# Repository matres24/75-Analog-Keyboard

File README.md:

# 75%-Analog-Keyboard
A custom-built mechanical keyboard featuring Hall effect sensors for analog key press detection. This project uses DRV5055A4 Hall sensors, magnets mounted in keycaps, and a CD74HC4067 multiplexer controlled by a microcontroller. Each key press is measured as a variable voltage, enabling analog input functionality. RGB LEDs (WS2812B) provide per-key lighting. This project is meant to fit into Monsgeek M1 case.

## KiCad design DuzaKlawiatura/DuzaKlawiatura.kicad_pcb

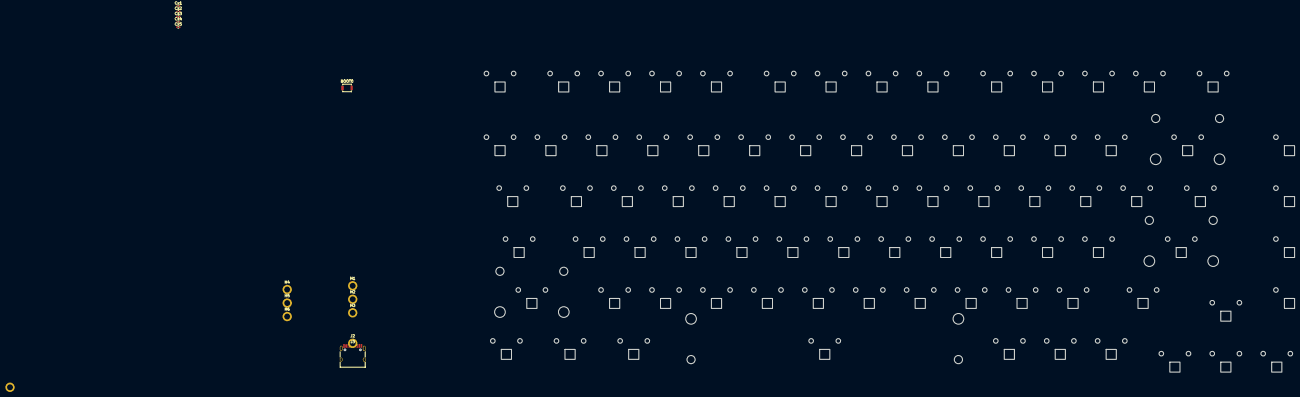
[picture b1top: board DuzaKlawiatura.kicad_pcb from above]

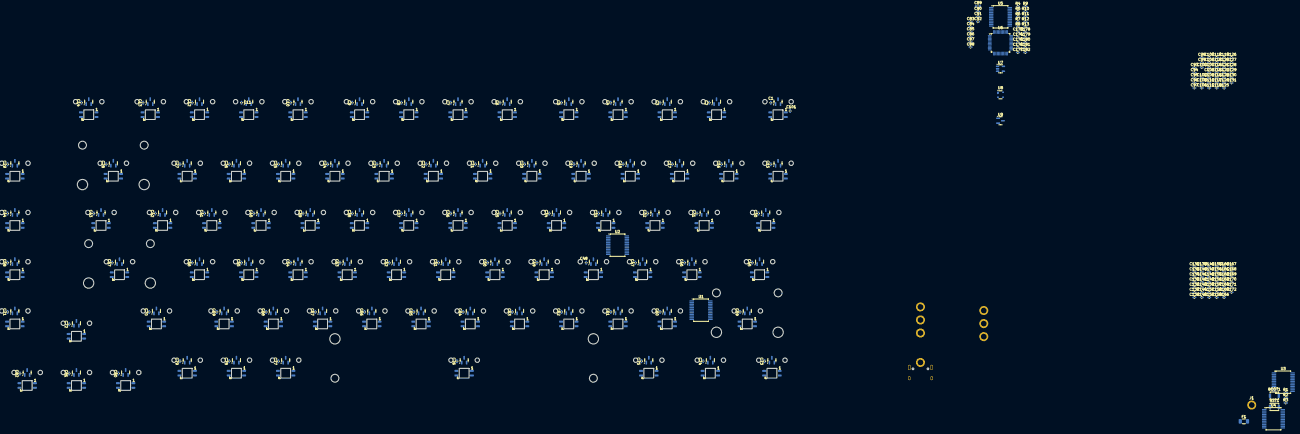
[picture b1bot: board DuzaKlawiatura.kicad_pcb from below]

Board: 2 copper layers, 386 parts (208 on the bottom side), 31 nets, no tracks yet.

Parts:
BOOT0, BOOT1: SW_SPST; SW_SPST_B3U-1000P
C1, C2, C3, C4, C5, C6, C7, C8, C9, C10, C11, C12, C13, C14, C15, C16, C17, C18, C19, C20, C21, C22, C23, C24, C25, C26, C27, C28, C29, C30, C31, C32, C33, C34, C35, C36, C37, C38, C39, C40, C41, C42, C43, C44, C45, C46, C47, C48, C49, C50, C51, C52, C53, C54, C55, C56, C57, C58, C59, C60, C61, C62, C63, C64, C65, C66, C67, C68, C69, C70, C71, C72, C73, C74, C75, C76, C77, C78, C79, C80, C81, C82, C98, C99, C100: 0,1u; C_0402_1005Metric
C83, C85, C86, C87: 10n; C_0402_1005Metric
C84: 10uF; C_0402_1005Metric
C88, C90, C91, C92, C93, C94, C97: 100nF; C_0402_1005Metric
C89: 10uF; C_0603_1608Metric
C95, C96: 1uF; C_0402_1005Metric
C101, C102, C103, C104, C105, C106, C107, C108, C109, C110, C111, C112, C113, C114, C115, C116, C117, C118, C119, C120, C121, C122, C123, C124, C125, C126, C127, C128, C129, C130, C131, C132, C133, C134, C135, C136, C137, C138, C139, C140, C141, C142, C143, C144, C145, C146, C147, C148, C149, C150, C151, C152, C153, C154, C155, C156, C157, C158, C159, C160, C161, C162, C163, C164, C165, C166, C167, C168, C169, C170, C171, C172, C173, C174, C175, C176, C177, C178, C179, C180, C181, C182: 100n; C_0402_1005Metric
Cx1, Cx2, Cx3, Cx4, Cx5: 100nF; C_0402_1005Metric
F1: 500mA; Fuse_1206_3216Metric
H1, H2, H3, H4, H5, H6: MountingHole; MountingHole_2.2mm_M2_ISO7380_Pad
J1, J2: Conn_01x02_Pin; MountingHole_2.2mm_M2_ISO7380_Pad
J3: USB_C_Receptacle_USB2.0; USB_C_Receptacle_HRO_TYPE-C-31-M-12
LED1, LED2, LED3, LED4, LED5, LED6, LED7, LED8, LED9, LED10, LED11, LED12, LED13, LED14, LED15, LED16, LED17, LED18, LED19, LED20, LED21, LED22, LED23, LED24, LED25, LED26, LED27, LED28, LED29, LED30, LED31, LED32, LED33, LED34, LED35, LED36, LED37, LED38, LED39, LED40, LED41, LED42, LED43, LED44, LED45, LED46, LED47, LED48, LED49, LED50, LED51, LED52, LED53, LED54, LED55, LED56, LED57, LED58, LED59, LED60, LED61, LED62, LED63, LED64, LED65, LED66, LED67, LED68, LED69, LED70, LED71, LED72, LED73, LED74, LED75, LED76, LED77, LED78, LED79, LED80, LED81, LED82: WS2812B; MX-LED_WS2812B_wide
R1, R2, R3, R4, R5, R6, R7, R8, R9, R10, R13: 10k; R_0402_1005Metric
R11, R12: 5.1k; R_0402_1005Metric
RST1: SW_SPST; SW_SPST_B3U-1000P
SW1, SW2, SW3, SW4, SW5, SW6, SW7, SW8, SW9, SW10, SW11, SW12, SW13, SW14, SW15, SW16, SW17, SW18, SW19, SW20, SW21, SW22, SW23, SW24, SW25, SW26, SW27, SW29, SW31, SW32, SW33, SW34, SW35, SW36, SW37, SW38, SW39, SW40, SW41, SW42, SW44, SW46, SW47, SW48, SW49, SW50, SW51, SW52, SW53, SW54, SW55, SW56, SW58, SW60, SW61, SW62, SW63, SW64, SW65, SW66, SW67, SW68, SW69, SW71, SW72, SW77, SW78, SW79, SW80, SW81, SW82: DRV5053; MX-Analog-1U
SW28: DRV5053; MX-Analog-2U
SW30, SW43: DRV5053; MX-Analog-1.5U
SW45, SW70: DRV5053; MX-Analog-1.75U
SW57, SW59: DRV5053; MX-Analog-2.25U
SW73, SW74, SW75: DRV5053; MX-Analog-1.25U
SW76: DRV5053; MX-Analog-6.25U-ReversedStabilizers
U1, U2, U3, U4, U5: CD74HC4067SM; SSOP-24_5.3x8.2mm_P0.65mm
U6: STM32F072CBT6; LQFP-48_7x7mm_P0.5mm
U7: SN74LV1T34DBV; SOT-23-5
U8: PRTR5V0U2X; SOT-143
U9: XC6206P332MR-Regulator_Linear; SOT-23

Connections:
+3V3: BOOT0.1 (A), BOOT1.1 (A), C89.1, C90.1, C91.1, C92.1, C93.1, C96.1, C97.1, U6.1 (VBAT), U6.9 (VDDA), U6.24 (VDD), U6.36 (VDDIO2), U6.48 (VDD), U9.2 (VO)
+5V: C1.1, C2.1, C3.1, C4.1, C5.1, C6.1, C7.1, C8.1, C9.1, C10.1, C11.1, C12.1, C13.1, C14.1, C15.1, C16.1, C17.1, C18.1, C19.1, C20.1, C21.1, C22.1, C23.1, C24.1, C25.1, C26.1, C27.1, C28.1, C29.1, C30.1, C31.1, C32.1, C33.1, C34.1, C35.1, C36.1, C37.1, C38.1, C39.1, C40.1, C41.1, C42.1, C43.1, C44.1, C45.1, C46.1, C47.1, C48.1, C49.1, C50.1, C51.1, C52.1, C53.1, C54.1, C55.1, C56.1, C57.1, C58.1, C59.1, C60.1, C61.1, C62.1, C63.1, C64.1, C65.1, C66.1, C67.1, C68.1, C69.1, C70.1, C71.1, C72.1, C73.1, C74.1, C75.1, C76.1, C77.1, C78.1, C79.1, C80.1, C81.1, C82.1, C88.1, C95.1, C98.1, C99.1, C100.1, C101.1, C102.1, C103.1, C104.1, C105.1, C106.1, C107.1, C108.1, C109.1, C110.1, C111.1, C112.1, C113.1, C114.1, C115.1, C116.1, C117.1, C118.1, C119.1, C120.1, C121.1, C122.1, C123.1, C124.1, C125.1, C126.1, C127.1, C128.1, C129.1, C130.1, C131.1, C132.1, C133.1, C134.1, C135.1, C136.1, C137.1, C138.1, C139.1, C140.1, C141.1, C142.1, C143.1, C144.1, C145.1, C146.1, C147.1, C148.1, C149.1, C150.1, C151.1, C152.1, C153.1, C154.1, C155.1, C156.1, C157.1, C158.1, C159.1, C160.1, C161.1, C162.1, C163.1, C164.1, C165.1, C166.1, C167.1, C168.1, C169.1, C170.1, C171.1, C172.1, C173.1, C174.1, C175.1, C176.1, C177.1, C178.1, C179.1, C180.1, C181.1, C182.1, Cx1.2, Cx2.2, Cx3.2, Cx4.2, Cx5.2, F1.2, LED1.1 (VCC), LED2.1 (VCC), LED3.1 (VCC), LED4.1 (VCC), LED5.1 (VCC), LED6.1 (VCC), LED7.1 (VCC), LED8.1 (VCC), LED9.1 (VCC), LED10.1 (VCC), LED11.1 (VCC), LED12.1 (VCC), LED13.1 (VCC), LED14.1 (VCC), LED15.1 (VCC), LED16.1 (VCC), LED17.1 (VCC), LED18.1 (VCC), LED19.1 (VCC), LED20.1 (VCC), LED21.1 (VCC), LED22.1 (VCC), LED23.1 (VCC), LED24.1 (VCC), LED25.1 (VCC), LED26.1 (VCC), LED27.1 (VCC), LED28.1 (VCC), LED29.1 (VCC), LED30.1 (VCC), LED31.1 (VCC), LED32.1 (VCC), LED33.1 (VCC), LED34.1 (VCC), LED35.1 (VCC), LED36.1 (VCC), LED37.1 (VCC), LED38.1 (VCC), LED39.1 (VCC), LED40.1 (VCC), LED41.1 (VCC), LED42.1 (VCC), LED43.1 (VCC), LED44.1 (VCC), LED45.1 (VCC), LED46.1 (VCC), LED47.1 (VCC), LED48.1 (VCC), LED49.1 (VCC), LED50.1 (VCC), LED51.1 (VCC), LED52.1 (VCC), LED53.1 (VCC), LED54.1 (VCC), LED55.1 (VCC), LED56.1 (VCC), LED57.1 (VCC), LED58.1 (VCC), LED59.1 (VCC), LED60.1 (VCC), LED61.1 (VCC), LED62.1 (VCC), LED63.1 (VCC), LED64.1 (VCC), LED65.1 (VCC), LED66.1 (VCC), LED67.1 (VCC), LED68.1 (VCC), LED69.1 (VCC), LED70.1 (VCC), LED71.1 (VCC), LED72.1 (VCC), LED73.1 (VCC), LED74.1 (VCC), LED75.1 (VCC), LED76.1 (VCC), LED77.1 (VCC), LED78.1 (VCC), LED79.1 (VCC), LED80.1 (VCC), LED81.1 (VCC), LED82.1 (VCC), SW1.1 (VCC), SW2.1 (VCC), SW3.1 (VCC), SW4.1 (VCC), SW5.1 (VCC), SW6.1 (VCC), SW7.1 (VCC), SW8.1 (VCC), SW9.1 (VCC), SW10.1 (VCC), SW11.1 (VCC), SW12.1 (VCC), SW13.1 (VCC), SW14.1 (VCC), SW15.1 (VCC), SW16.1 (VCC), SW17.1 (VCC), SW18.1 (VCC), SW19.1 (VCC), SW20.1 (VCC), SW21.1 (VCC), SW22.1 (VCC), SW23.1 (VCC), SW24.1 (VCC), SW25.1 (VCC), SW26.1 (VCC), SW27.1 (VCC), SW28.1 (VCC), SW29.1 (VCC), SW30.1 (VCC), SW31.1 (VCC), SW32.1 (VCC), SW33.1 (VCC), SW34.1 (VCC), SW35.1 (VCC), SW36.1 (VCC), SW37.1 (VCC), SW38.1 (VCC), SW39.1 (VCC), SW40.1 (VCC), SW41.1 (VCC), SW42.1 (VCC), SW43.1 (VCC), SW44.1 (VCC), SW45.1 (VCC), SW46.1 (VCC), SW47.1 (VCC), SW48.1 (VCC), SW49.1 (VCC), SW50.1 (VCC), SW51.1 (VCC), SW52.1 (VCC), SW53.1 (VCC), SW54.1 (VCC), SW55.1 (VCC), SW56.1 (VCC), SW57.1 (VCC), SW58.1 (VCC), SW59.1 (VCC), SW60.1 (VCC), SW61.1 (VCC), SW62.1 (VCC), SW63.1 (VCC), SW64.1 (VCC), SW65.1 (VCC), SW66.1 (VCC), SW67.1 (VCC), SW68.1 (VCC), SW69.1 (VCC), SW70.1 (VCC), SW71.1 (VCC), SW72.1 (VCC), SW73.1 (VCC), SW74.1 (VCC), SW75.1 (VCC), SW76.1 (VCC), SW77.1 (VCC), SW78.1 (VCC), SW79.1 (VCC), SW80.1 (VCC), SW81.1 (VCC), SW82.1 (VCC), U1.24 (VCC), U2.24 (VCC), U3.24 (VCC), U4.24 (VCC), U5.24 (VCC), U7.5 (VCC), U8.4 (VCC), U9.3 (VI)
BOOT0: BOOT0.2 (B), BOOT1.2 (B), R13.1, U6.44 (BOOT0)
COM: C83.1, R1.2, R4.1, U6.11 (PA1)
COM1: C84.1, R2.2, R5.1, U6.12 (PA2)
COM2: C85.1, R3.2, R6.1, U6.13 (PA3)
COM3: C86.1, R7.2, R9.1, U6.14 (PA4)
COM4: C87.1, R8.2, R10.1, U6.15 (PA5)
D+: J3.A6 (D+), J3.B6 (D+), U6.33 (PA12), U8.3 (I/O2)
D-: J3.A7 (D-), J3.B7 (D-), U6.32 (PA11), U8.2 (I/O1)
E: U1.15 (~E), U6.40 (PB4)
E1: U2.15 (~E), U6.41 (PB5)
E2: U3.15 (~E), U6.42 (PB6)
E3: U4.15 (~E), U6.43 (PB7)
E4: U5.15 (~E), U6.45 (PB8)
GND: C1.2, C2.2, C3.2, C4.2, C5.2, C6.2, C7.2, C8.2, C9.2, C10.2, C11.2, C12.2, C13.2, C14.2, C15.2, C16.2, C17.2, C18.2, C19.2, C20.2, C21.2, C22.2, C23.2, C24.2, C25.2, C26.2, C27.2, C28.2, C29.2, C30.2, C31.2, C32.2, C33.2, C34.2, C35.2, C36.2, C37.2, C38.2, C39.2, C40.2, C41.2, C42.2, C43.2, C44.2, C45.2, C46.2, C47.2, C48.2, C49.2, C50.2, C51.2, C52.2, C53.2, C54.2, C55.2, C56.2, C57.2, C58.2, C59.2, C60.2, C61.2, C62.2, C63.2, C64.2, C65.2, C66.2, C67.2, C68.2, C69.2, C70.2, C71.2, C72.2, C73.2, C74.2, C75.2, C76.2, C77.2, C78.2, C79.2, C80.2, C81.2, C82.2, C83.2, C84.2, C85.2, C86.2, C87.2, C88.2, C89.2, C90.2, C91.2, C92.2, C93.2, C94.2, C95.2, C96.2, C97.2, C98.2, C99.2, C100.2, C101.2, C102.2, C103.2, C104.2, C105.2, C106.2, C107.2, C108.2, C109.2, C110.2, C111.2, C112.2, C113.2, C114.2, C115.2, C116.2, C117.2, C118.2, C119.2, C120.2, C121.2, C122.2, C123.2, C124.2, C125.2, C126.2, C127.2, C128.2, C129.2, C130.2, C131.2, C132.2, C133.2, C134.2, C135.2, C136.2, C137.2, C138.2, C139.2, C140.2, C141.2, C142.2, C143.2, C144.2, C145.2, C146.2, C147.2, C148.2, C149.2, C150.2, C151.2, C152.2, C153.2, C154.2, C155.2, C156.2, C157.2, C158.2, C159.2, C160.2, C161.2, C162.2, C163.2, C164.2, C165.2, C166.2, C167.2, C168.2, C169.2, C170.2, C171.2, C172.2, C173.2, C174.2, C175.2, C176.2, C177.2, C178.2, C179.2, C180.2, C181.2, C182.2, Cx1.1, Cx2.1, Cx3.1, Cx4.1, Cx5.1, J3.A1 (GND), J3.A12 (GND), J3.B1 (GND), J3.B12 (GND), J3.S1 (SHIELD), LED1.3 (GND), LED2.3 (GND), LED3.3 (GND), LED4.3 (GND), LED5.3 (GND), LED6.3 (GND), LED7.3 (GND), LED8.3 (GND), LED9.3 (GND), LED10.3 (GND), LED11.3 (GND), LED12.3 (GND), LED13.3 (GND), LED14.3 (GND), LED15.3 (GND), LED16.3 (GND), LED17.3 (GND), LED18.3 (GND), LED19.3 (GND), LED20.3 (GND), LED21.3 (GND), LED22.3 (GND), LED23.3 (GND), LED24.3 (GND), LED25.3 (GND), LED26.3 (GND), LED27.3 (GND), LED28.3 (GND), LED29.3 (GND), LED30.3 (GND), LED31.3 (GND), LED32.3 (GND), LED33.3 (GND), LED34.3 (GND), LED35.3 (GND), LED36.3 (GND), LED37.3 (GND), LED38.3 (GND), LED39.3 (GND), LED40.3 (GND), LED41.3 (GND), LED42.3 (GND), LED43.3 (GND), LED44.3 (GND), LED45.3 (GND), LED46.3 (GND), LED47.3 (GND), LED48.3 (GND), LED49.3 (GND), LED50.3 (GND), LED51.3 (GND), LED52.3 (GND), LED53.3 (GND), LED54.3 (GND), LED55.3 (GND), LED56.3 (GND), LED57.3 (GND), LED58.3 (GND), LED59.3 (GND), LED60.3 (GND), LED61.3 (GND), LED62.3 (GND), LED63.3 (GND), LED64.3 (GND), LED65.3 (GND), LED66.3 (GND), LED67.3 (GND), LED68.3 (GND), LED69.3 (GND), LED70.3 (GND), LED71.3 (GND), LED72.3 (GND), LED73.3 (GND), LED74.3 (GND), LED75.3 (GND), LED76.3 (GND), LED77.3 (GND), LED78.3 (GND), LED79.3 (GND), LED80.3 (GND), LED81.3 (GND), LED82.3 (GND), R4.2, R5.2, R6.2, R9.2, R10.2, R11.1, R12.2, R13.2, RST1.2 (B), SW1.3 (GND), SW2.3 (GND), SW3.3 (GND), SW4.3 (GND), SW5.3 (GND), SW6.3 (GND), SW7.3 (GND), SW8.3 (GND), SW9.3 (GND), SW10.3 (GND), SW11.3 (GND), SW12.3 (GND), SW13.3 (GND), SW14.3 (GND), SW15.3 (GND), SW16.3 (GND), SW17.3 (GND), SW18.3 (GND), SW19.3 (GND), SW20.3 (GND), SW21.3 (GND), SW22.3 (GND), SW23.3 (GND), SW24.3 (GND), SW25.3 (GND), SW26.3 (GND), SW27.3 (GND), SW28.3 (GND), SW29.3 (GND), SW30.3 (GND), SW31.3 (GND), SW32.3 (GND), SW33.3 (GND), SW34.3 (GND), SW35.3 (GND), SW36.3 (GND), SW37.3 (GND), SW38.3 (GND), SW39.3 (GND), SW40.3 (GND), SW41.3 (GND), SW42.3 (GND), SW43.3 (GND), SW44.3 (GND), SW45.3 (GND), SW46.3 (GND), SW47.3 (GND), SW48.3 (GND), SW49.3 (GND), SW50.3 (GND), SW51.3 (GND), SW52.3 (GND), SW53.3 (GND), SW54.3 (GND), SW55.3 (GND), SW56.3 (GND), SW57.3 (GND), SW58.3 (GND), SW59.3 (GND), SW60.3 (GND), SW61.3 (GND), SW62.3 (GND), SW63.3 (GND), SW64.3 (GND), SW65.3 (GND), SW66.3 (GND), SW67.3 (GND), SW68.3 (GND), SW69.3 (GND), SW70.3 (GND), SW71.3 (GND), SW72.3 (GND), SW73.3 (GND), SW74.3 (GND), SW75.3 (GND), SW76.3 (GND), SW77.3 (GND), SW78.3 (GND), SW79.3 (GND), SW80.3 (GND), SW81.3 (GND), SW82.3 (GND), U1.12 (GND), U2.12 (GND), U3.12 (GND), U4.12 (GND), U5.12 (GND), U6.8 (VSSA), U6.23 (VSS), U6.35 (VSS), U6.47 (VSS), U7.3 (GND), U8.1 (GND), U9.1 (GND)
LED0: U6.29 (PA8), U7.2 (A)
LED_IN: LED1.4 (DIN), LED42.4 (DIN), U7.4 (Y)
NRST: C94.1, RST1.1 (A), U6.7 (NRST)
unnamed: J3.A5 (CC1), R11.2
unnamed: J3.B5 (CC2), R12.1
unnamed: R1.1, U1.1 (COM)
unnamed: R2.1, U2.1 (COM)
unnamed: R3.1, U3.1 (COM)
unnamed: R7.1, U4.1 (COM)
unnamed: R8.1, U5.1 (COM)
S0: U1.10 (S0), U2.10 (S0), U3.10 (S0), U4.10 (S0), U5.10 (S0), U6.18 (PB0)
S1: U1.11 (S1), U2.11 (S1), U3.11 (S1), U4.11 (S1), U5.11 (S1), U6.19 (PB1)
S2: U1.14 (S2), U2.14 (S2), U3.14 (S2), U4.14 (S2), U5.14 (S2), U6.20 (PB2)
S3: U1.13 (S3), U2.13 (S3), U3.13 (S3), U4.13 (S3), U5.13 (S3), U6.39 (PB3)
VBUS: F1.1, J3.A4 (VBUS), J3.A9 (VBUS), J3.B4 (VBUS), J3.B9 (VBUS)

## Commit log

2025-06-11 Pliki KiCad
2025-06-11 Added photos of layout and schematic, updated Kicad files.
